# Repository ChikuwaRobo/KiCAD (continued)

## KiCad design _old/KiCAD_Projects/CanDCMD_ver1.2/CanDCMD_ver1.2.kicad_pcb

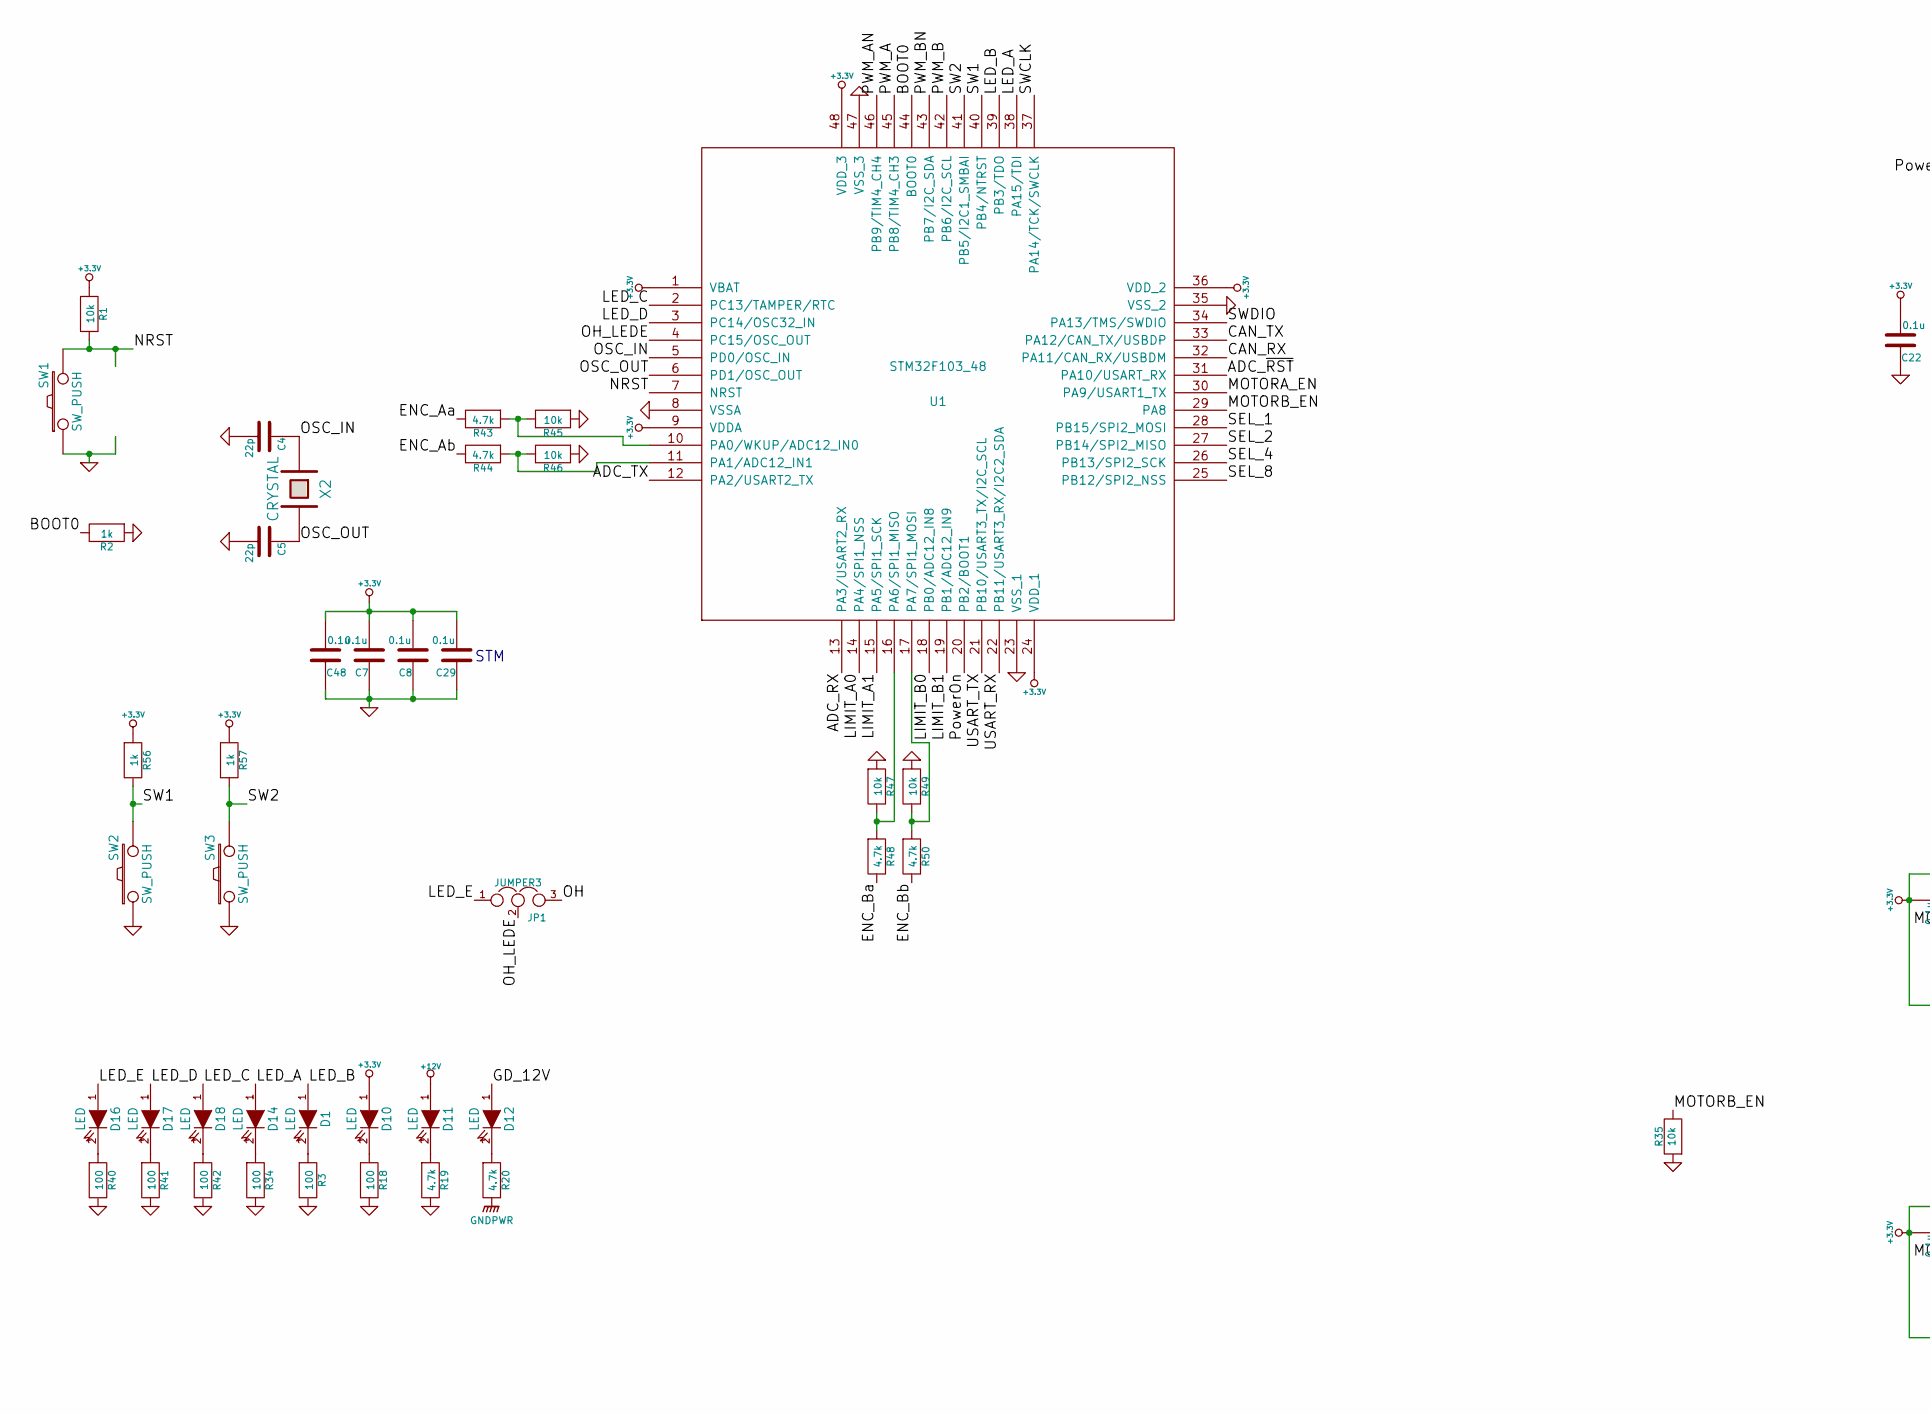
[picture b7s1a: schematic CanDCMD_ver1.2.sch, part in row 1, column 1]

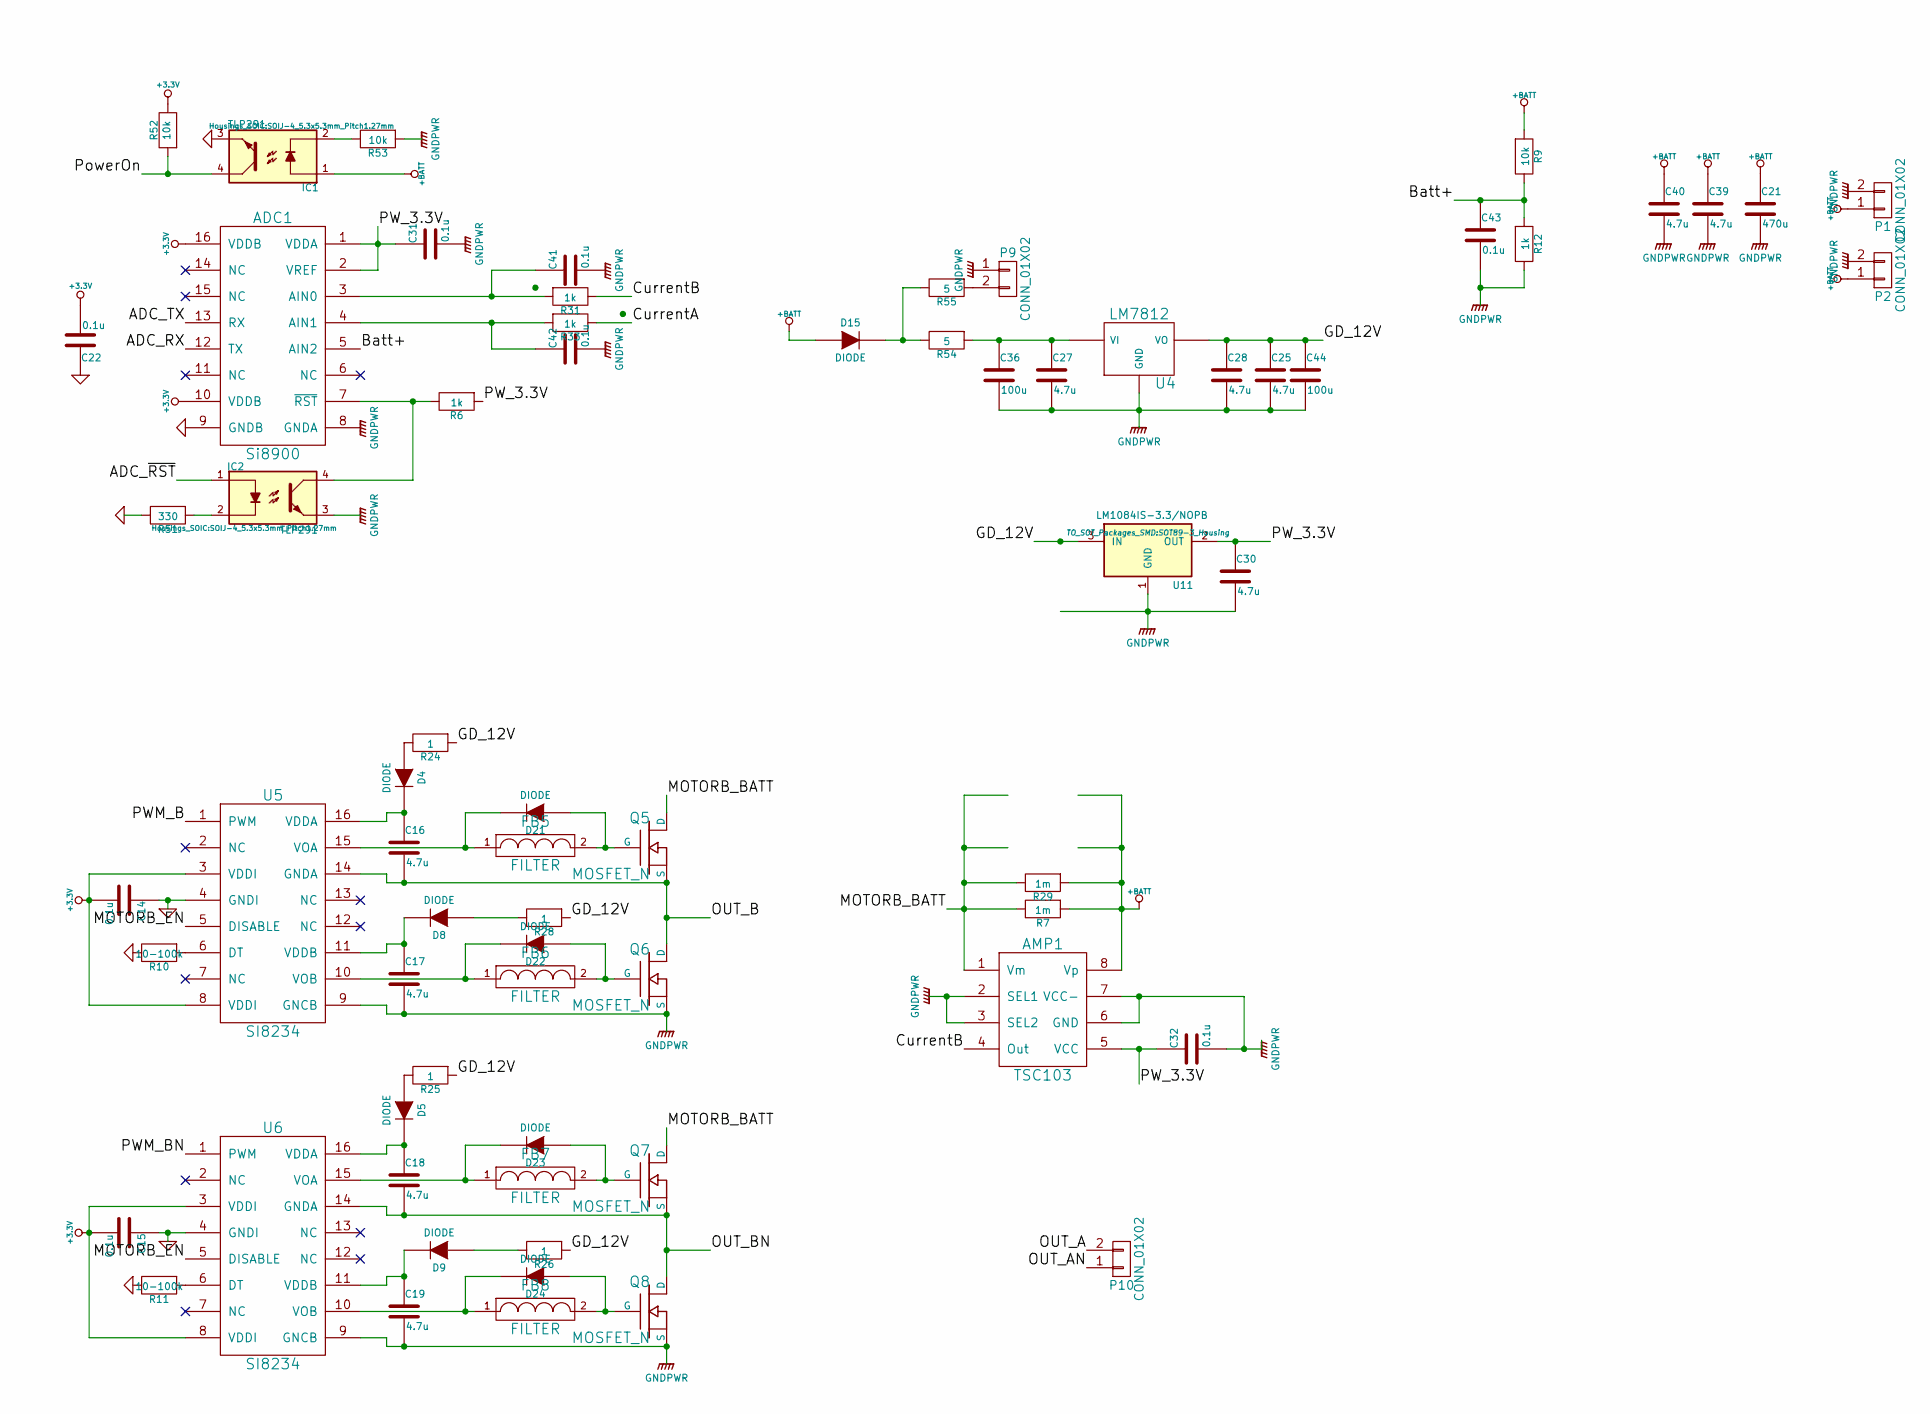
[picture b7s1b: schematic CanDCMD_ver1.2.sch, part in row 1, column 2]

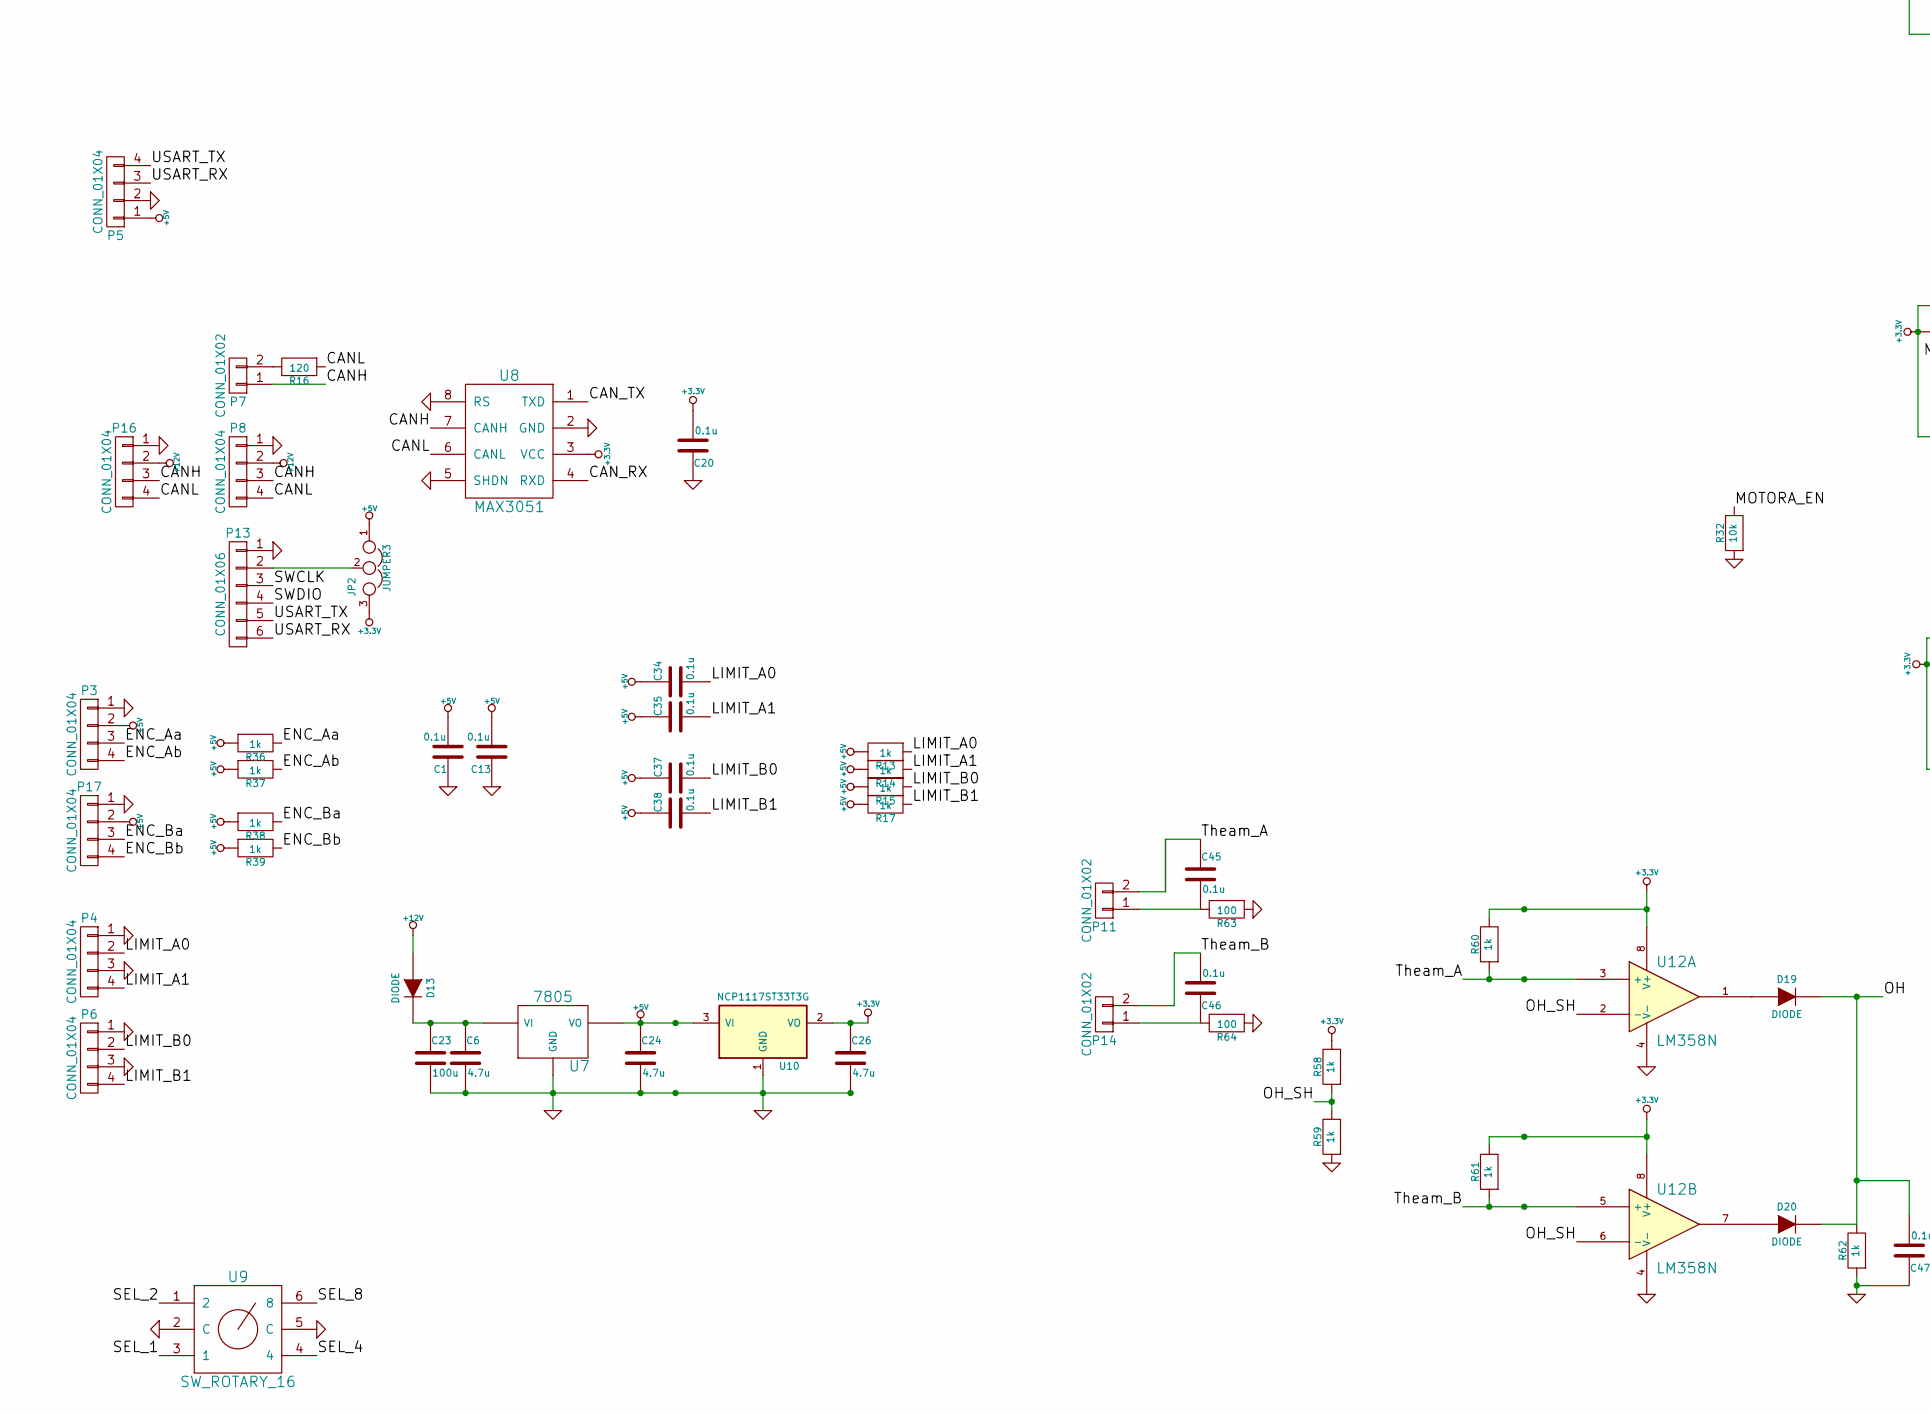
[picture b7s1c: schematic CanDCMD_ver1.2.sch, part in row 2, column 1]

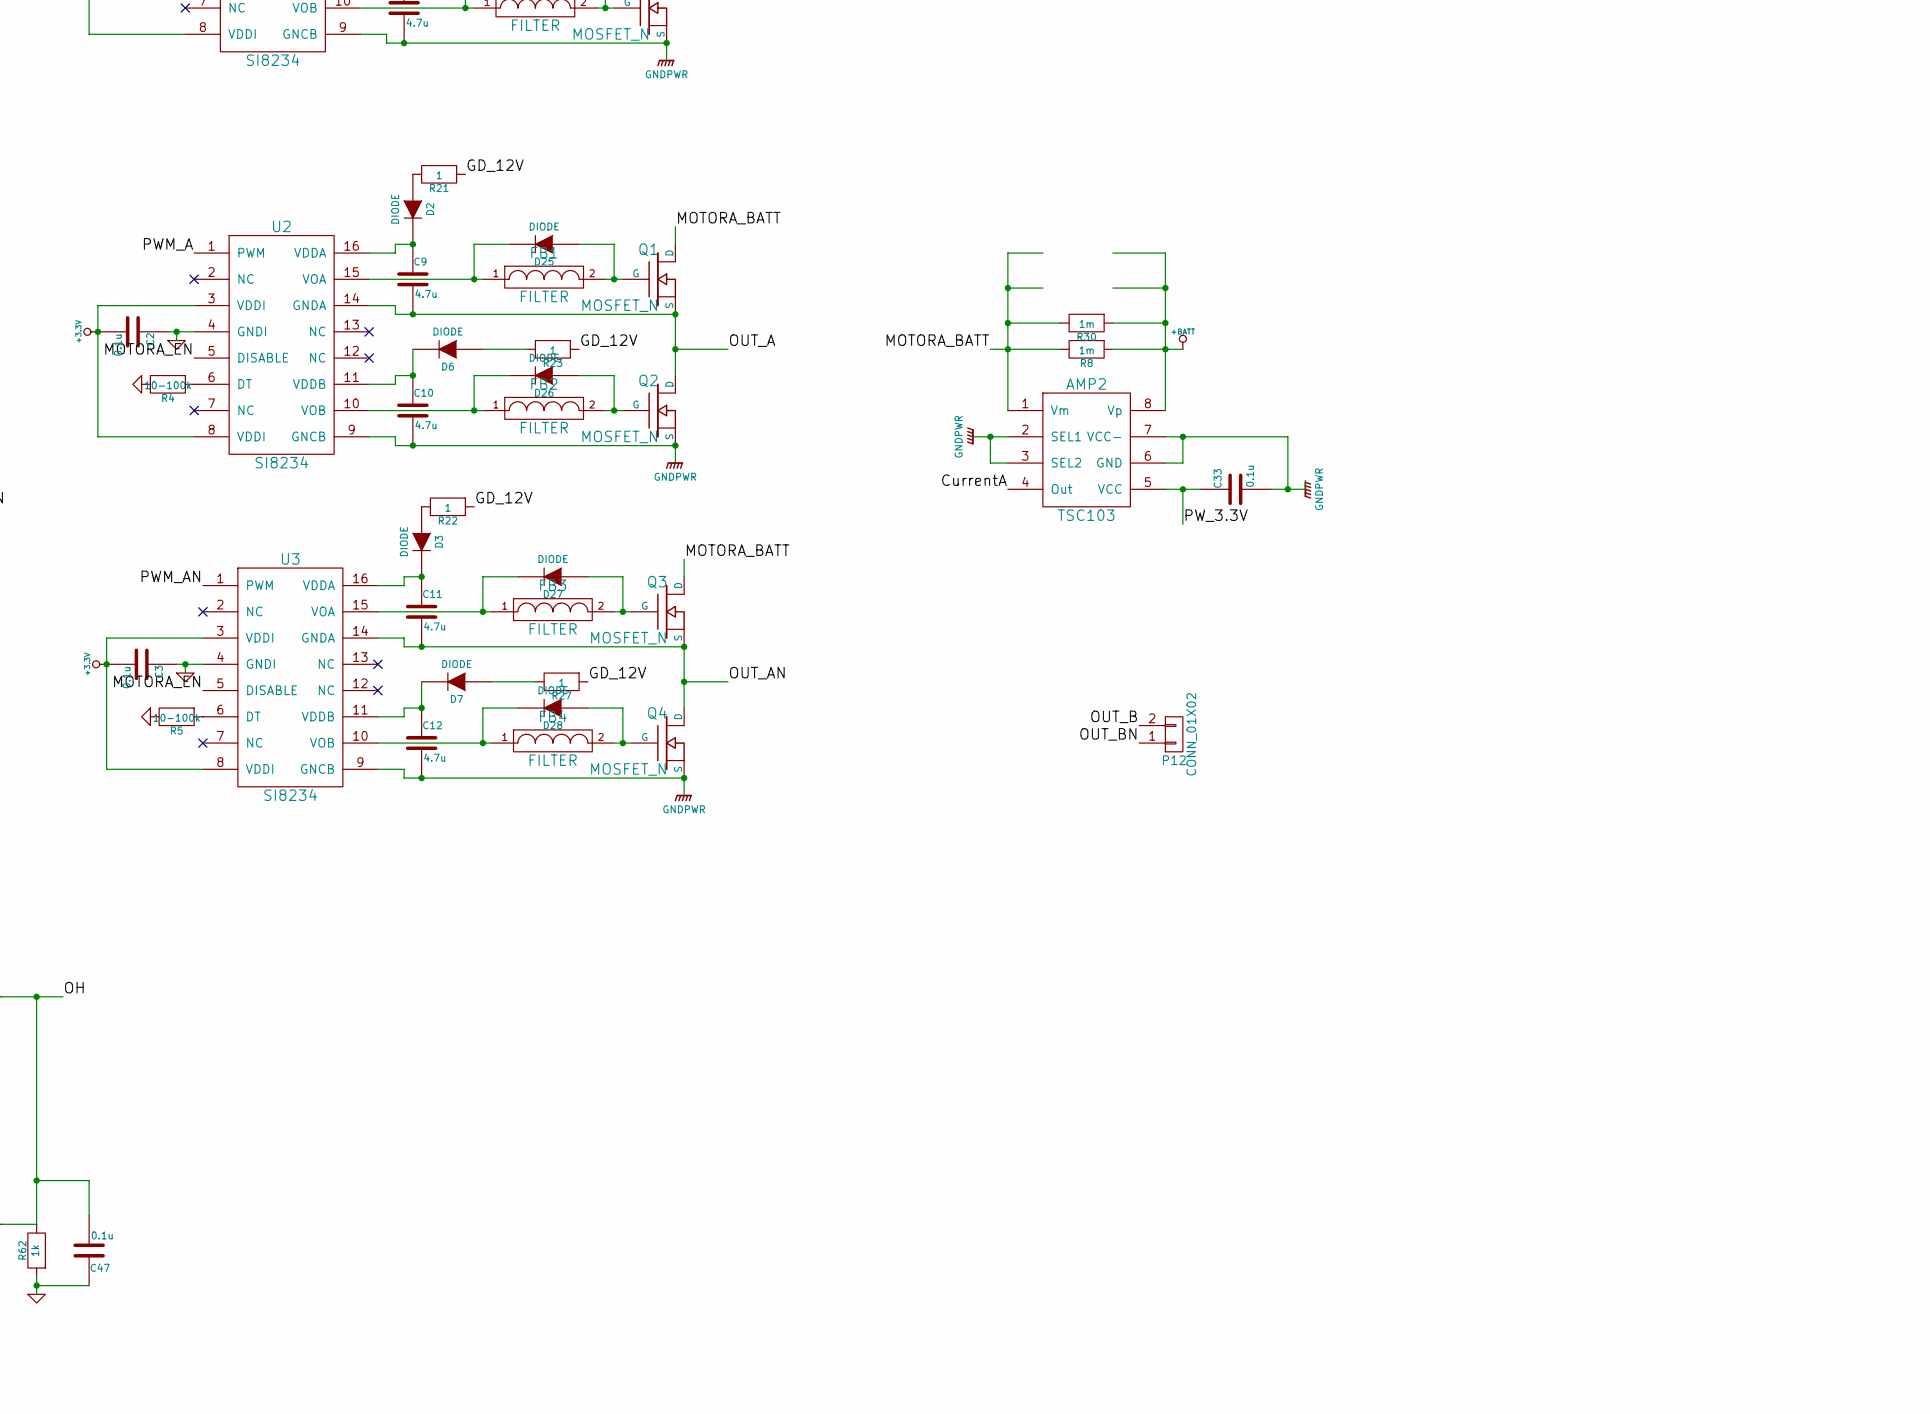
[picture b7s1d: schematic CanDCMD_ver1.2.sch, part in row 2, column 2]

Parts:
ADC1: Si8900; SOIC-16_7.5x10.3mm_Pitch1.27mm
AMP1, AMP2: TSC103; SOIC-8_3.9x4.9mm_Pitch1.27mm
C1, C2, C3, C7, C8, C13, C14, C15, C20, C22, C29, C31, C32, C33, C34, C35, C37, C38, C41, C42, C43, C45, C46, C47, C48: 0.1u; C1608_WP
C4, C5: 22p; C1608_WP
C6, C9, C10, C11, C12, C16, C17, C18, C19, C24, C25, C26, C27, C28, C30, C39, C40: 4.7u; C3216
C21: 470u; C_Radial_D12.5_L25_P5
C23, C36, C44: 100u; C_Radial_D6.3_L11.2_P2.5
D1, D10, D11, D12, D14, D16, D17, D18: LED; C1608_WP
D2, D3, D4, D5, D6, D7, D8, D9, D19, D20, D21, D22, D23, D24, D25, D26, D27, D28: DIODE; C1608_WP
D13, D15: DIODE; C3216
FB1, FB2, FB3, FB4, FB5, FB6, FB7, FB8: FILTER; C1608_WP
IC1, IC2: TLP291; SOIJ-4_5.3x5.3mm_Pitch1.27mm
JP1, JP2: JUMPER3; GS3
P1: CONN_01X02; DEANS_T_M
P2: CONN_01X02; DEANS_T_F
P3, P4, P6, P8, P16, P17: CONN_01X04; XA_4LC
P5: CONN_01X04; Socket_Strip_Straight_1x04
P7: CONN_01X02; Pin_Header_Straight_1x02
P9: CONN_01X02; XA_2T
P10, P12: CONN_01X02; DEANS_T_F_minPad
P11, P14: CONN_01X02; C3216_S
P13: CONN_01X06; ZH_6T
Q1, Q2, Q3, Q4, Q5, Q6, Q7, Q8: MOSFET_N; D2-PAK_compact
R1, R9, R32, R35, R45, R46, R47, R49, R52, R53: 10k; C1608_WP
R2, R6, R12, R13, R14, R15, R17, R31, R33, R36, R37, R38, R39, R56, R57, R58, R59, R60, R61, R62: 1k; C1608_WP
R3, R18, R34, R40, R41, R42, R63, R64: 100; C1608_WP
R4, R5, R10, R11: 10-100k; C1608_WP
R7, R8, R29, R30: 1m; R5025
R16: 120; C1608_WP
R19, R20, R43, R44, R48, R50: 4.7k; C1608_WP
R21, R22, R23, R24, R25, R26, R27, R28: 1; C1608_WP
R51: 330; C1608_WP
R54, R55: 5; R_2812
SW1, SW2, SW3: SW_PUSH; RP_SMD_Button
U1: STM32F103_48; LQFP-48_7x7mm_Pitch0.5mm
U2, U3, U5, U6: SI8234; SOIC-16_3.9x9.9mm_Pitch1.27mm
U4: LM7812; TO-252-2Lead_regu
U7: 7805; TO-252-2Lead_regu
U8: MAX3051; SOIC-8_3.9x4.9mm_Pitch1.27mm
U9: SW_ROTARY_16; rotary_0F
U10: NCP1117ST33T3G; SOT-223_reg
U11: LM1084IS-3.3/NOPB; SOT89-3_Housing
U12: LM358N; SOIC-8_3.9x4.9mm_Pitch1.27mm
X2: CRYSTAL; ABM3_2pads

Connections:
+3.3V: ADC1.10 (VDDB), ADC1.16 (VDDB), C2.2, C3.2, C7.2, C8.2, C14.2, C15.2, C20.2, C22.2, C26.1, C29.2, C48.2, D10.1 (A), JP2.3, R1.1, R52.2, R56.1, R57.1, R58.2, R60.2, R61.2, U1.1 (VBAT), U1.9 (VDDA), U1.24 (VDD_1), U1.36 (VDD_2), U1.48 (VDD_3), U2.3 (VDDI), U2.8 (VDDI), U3.3 (VDDI), U3.8 (VDDI), U5.3 (VDDI), U5.8 (VDDI), U6.3 (VDDI), U6.8 (VDDI), U8.3 (VCC), U10.2 (VO), U12.8 (V+)
+5V: C1.2, C13.2, C24.1, C34.1, C35.1, C37.1, C38.1, JP2.1, P3.2, P5.1, P17.2, R13.2, R14.2, R15.2, R17.2, R36.1, R37.1, R38.1, R39.1, U7.VO, U10.3 (VI)
+12V: D11.1 (A), D13.1 (A), P8.2, P16.2
+BATT: AMP1.8 (Vp), AMP2.8 (Vp), C21.1, C39.1, C40.1, D15.1 (A), IC1.1, P1.1, P2.1, R7.1, R8.1, R9.1, R29.1, R30.1
/ADC_RX: ADC1.12 (TX), U1.13 (PA3/USART2_RX)
/ADC_TX: ADC1.13 (RX), U1.12 (PA2/USART2_TX)
/ADC_~RST: IC2.1, U1.31 (PA10/USART_RX)
/BOOT0: R2.2, U1.44 (BOOT0)
/Batt+: ADC1.5 (AIN2), C43.1, R9.2, R12.1
/CANH: P7.1, P8.3, P16.3, U8.7 (CANH)
/CANL: P8.4, P16.4, R16.1, U8.6 (CANL)
/CAN_RX: U1.32 (PA11/CAN_RX/USBDM), U8.4 (RXD)
/CAN_TX: U1.33 (PA12/CAN_TX/USBDP), U8.1 (TXD)
/CurrentA: AMP2.4 (Out), R33.2
/CurrentB: AMP1.4 (Out), R31.2
/ENC_Aa: P3.3, R36.2, R43.2
/ENC_Ab: P3.4, R37.2, R44.2
/ENC_Ba: P17.3, R38.2, R48.2
/ENC_Bb: P17.4, R39.2, R50.2
/GD_12V: C25.1, C28.1, C44.1, D12.1 (A), R21.1, R22.1, R23.1, R24.1, R25.1, R26.1, R27.1, R28.1, U4.VO, U11.3 (IN)
/LED_A: D14.1 (A), U1.38 (PA15/TDI)
/LED_B: D1.1 (A), U1.39 (PB3/TDO)
/LED_C: D18.1 (A), U1.2 (PC13/TAMPER/RTC)
/LED_D: D17.1 (A), U1.3 (PC14/OSC32_IN)
/LED_E: D16.1 (A), JP1.1
/LIMIT_A0: C34.2, P4.2, R13.1, U1.14 (PA4/SPI1_NSS)
/LIMIT_A1: C35.2, P4.4, R14.1, U1.15 (PA5/SPI1_SCK)
/LIMIT_B0: C37.2, P6.2, R15.1, U1.18 (PB0/ADC12_IN8)
/LIMIT_B1: C38.2, P6.4, R17.1, U1.19 (PB1/ADC12_IN9)
/MOTORA_BATT: AMP2.1 (Vm), Q1.D, Q3.D, R8.2, R30.2
/MOTORA_EN: R32.2, U1.30 (PA9/USART1_TX), U2.5 (DISABLE), U3.5 (DISABLE)
/MOTORB_BATT: AMP1.1 (Vm), Q5.D, Q7.D, R7.2, R29.2
/MOTORB_EN: R35.2, U1.29 (PA8), U5.5 (DISABLE), U6.5 (DISABLE)
/NRST: R1.2, SW1.2, U1.7 (NRST)
/OH: C47.2, D19.2 (K), D20.2 (K), JP1.3, R62.2
/OH_LEDE: JP1.2, U1.4 (PC15/OSC_OUT)
/OH_SH: R58.1, R59.2, U12.2 (-), U12.6 (-)
/OSC_IN: C4.1, U1.5 (PD0/OSC_IN), X2.1
/OSC_OUT: C5.1, U1.6 (PD1/OSC_OUT), X2.2
/OUT_A: C9.2, P10.2, Q1.S, Q2.D, U2.14 (GNDA)
/OUT_AN: C11.2, P10.1, Q3.S, Q4.D, U3.14 (GNDA)
/OUT_B: C16.2, P12.2, Q5.S, Q6.D, U5.14 (GNDA)
/OUT_BN: C18.2, P12.1, Q7.S, Q8.D, U6.14 (GNDA)
/PWM_A: U1.45 (PB8/TIM4_CH3), U2.1 (PWM)
/PWM_AN: U1.46 (PB9/TIM4_CH4), U3.1 (PWM)
/PWM_B: U1.42 (PB6/I2C_SCL), U5.1 (PWM)
/PWM_BN: U1.43 (PB7/I2C_SDA), U6.1 (PWM)
/PW_3.3V: ADC1.1 (VDDA), ADC1.2 (VREF), AMP1.5 (VCC), AMP2.5 (VCC), C30.1, C31.1, C32.1, C33.1, R6.1, U11.2 (OUT)
/PowerOn: IC1.4, R52.1, U1.20 (PB2/BOOT1)
/SEL_1: U1.28 (PB15/SPI2_MOSI), U9.3 (1)
/SEL_2: U1.27 (PB14/SPI2_MISO), U9.1 (2)
/SEL_4: U1.26 (PB13/SPI2_SCK), U9.4
/SEL_8: U1.25 (PB12/SPI2_NSS), U9.6 (8)
/SW1: R56.2, SW2.2, U1.40 (PB4/NTRST)
/SW2: R57.2, SW3.2, U1.41 (PB5/I2C1_SMBAI)
/SWCLK: P13.3, U1.37 (PA14/TCK/SWCLK)
/SWDIO: P13.4, U1.34 (PA13/TMS/SWDIO)
/Theam_A: C45.1, P11.2, R60.1, U12.3 (+)
/Theam_B: C46.2, P14.2, R61.1, U12.5 (+)
/USART_RX: P5.3, P13.6, U1.22 (PB11/USART3_RX/I2C2_SDA)
/USART_TX: P5.4, P13.5, U1.21 (PB10/USART3_TX/I2C_SCL)
GND: ADC1.9 (GNDB), C1.1, C2.1, C3.1, C4.2, C5.2, C6.2, C7.1, C8.1, C13.1, C14.1, C15.1, C20.1, C22.1, C23.2, C24.2, C26.2, C29.1, C47.1, C48.1, IC1.3, P3.1, P4.1, P4.3, P5.2, P6.1, P6.3, P8.1, P13.1, P16.1, P17.1, R2.1, R3.2, R4.2, R5.2, R10.2, R11.2, R18.2, R19.2, R32.1, R34.2, R35.1, R40.2, R41.2, R42.2, R45.1, R46.1, R47.1, R49.1, R51.2, R59.1, R62.1, R63.1, R64.1, SW1.1, SW2.1, SW3.1, U1.8 (VSSA), U1.23 (VSS_1), U1.35 (VSS_2), U1.47 (VSS_3), U2.4 (GNDI), U3.4 (GNDI), U5.4 (GNDI), U6.4 (GNDI), U7.GND, U8.2 (GND), U8.5 (SHDN), U8.8 (RS), U9.2 (C), U9.5 (C), U10.1 (GND), U12.4 (V-)
GNDPWR: ADC1.8 (GNDA), AMP1.2 (SEL1), AMP1.3 (SEL2), AMP1.6 (GND), AMP1.7 (VCC-), AMP2.2 (SEL1), AMP2.3 (SEL2), AMP2.6 (GND), AMP2.7 (VCC-), C10.2, C12.2, C17.2, C19.2, C21.2, C25.2, C27.2, C28.2, C30.2, C31.2, C32.2, C33.2, C36.2, C39.2, C40.2, C41.2, C42.2, C43.2, C44.2, IC2.3, P1.2, P2.2, P9.1, Q2.S, Q4.S, Q6.S, Q8.S, R12.2, R20.2, R53.1, U2.9 (GNCB), U3.9 (GNCB), U4.GND, U5.9 (GNCB), U6.9 (GNCB), U11.1 (GND)
unnamed: ADC1.3 (AIN0), C41.1, R31.1
unnamed: ADC1.4 (AIN1), C42.1, R33.1
unnamed: ADC1.7 (~RST), IC2.4, R6.2
unnamed: C9.1, D2.2 (K), U2.16 (VDDA)
unnamed: C10.1, D6.2 (K), U2.11 (VDDB)
unnamed: C11.1, D3.2 (K), U3.16 (VDDA)
unnamed: C12.1, D7.2 (K), U3.11 (VDDB)
unnamed: C16.1, D4.2 (K), U5.16 (VDDA)
unnamed: C17.1, D8.2 (K), U5.11 (VDDB)
unnamed: C18.1, D5.2 (K), U6.16 (VDDA)
unnamed: C19.1, D9.2 (K), U6.11 (VDDB)
unnamed: C6.1, C23.1, D13.2 (K), U7.VI
unnamed: C27.1, C36.1, R54.1, U4.VI
unnamed: C45.2, P11.1, R63.2
unnamed: C46.1, P14.1, R64.2
unnamed: D1.2 (K), R3.1
unnamed: D2.1 (A), R21.2
unnamed: D3.1 (A), R22.2
unnamed: D4.1 (A), R24.2
unnamed: D5.1 (A), R25.2
unnamed: D6.1 (A), R23.2
unnamed: D7.1 (A), R27.2
unnamed: D8.1 (A), R28.2
unnamed: D9.1 (A), R26.2
unnamed: D10.2 (K), R18.1
unnamed: D11.2 (K), R19.1
unnamed: D12.2 (K), R20.1
unnamed: D14.2 (K), R34.1
unnamed: D15.2 (K), R54.2, R55.2
unnamed: D16.2 (K), R40.1
unnamed: D17.2 (K), R41.1
unnamed: D18.2 (K), R42.1
unnamed: D19.1 (A), U12.1
unnamed: D20.1 (A), U12.7
unnamed: D21.1 (A), FB5.2, Q5.G
unnamed: D21.2 (K), FB5.1, U5.15 (VOA)
unnamed: D22.1 (A), FB6.2, Q6.G
unnamed: D22.2 (K), FB6.1, U5.10 (VOB)
unnamed: D23.1 (A), FB7.2, Q7.G
unnamed: D23.2 (K), FB7.1, U6.15 (VOA)
unnamed: D24.1 (A), FB8.2, Q8.G
unnamed: D24.2 (K), FB8.1, U6.10 (VOB)
unnamed: D25.1 (A), FB1.2, Q1.G
unnamed: D25.2 (K), FB1.1, U2.15 (VOA)
unnamed: D26.1 (A), FB2.2, Q2.G
unnamed: D26.2 (K), FB2.1, U2.10 (VOB)
unnamed: D27.1 (A), FB3.2, Q3.G
unnamed: D27.2 (K), FB3.1, U3.15 (VOA)
unnamed: D28.1 (A), FB4.2, Q4.G
unnamed: D28.2 (K), FB4.1, U3.10 (VOB)
unnamed: IC1.2, R53.2
unnamed: IC2.2, R51.1
unnamed: JP2.2, P13.2
unnamed: P7.2, R16.2
unnamed: P9.2, R55.1
unnamed: R4.1, U2.6 (DT)
unnamed: R5.1, U3.6 (DT)
unnamed: R10.1, U5.6 (DT)
unnamed: R11.1, U6.6 (DT)
unnamed: R43.1, R45.2, U1.10 (PA0/WKUP/ADC12_IN0)
unnamed: R44.1, R46.2, U1.11 (PA1/ADC12_IN1)
unnamed: R47.2, R48.1, U1.16 (PA6/SPI1_MISO)
unnamed: R49.2, R50.1, U1.17 (PA7/SPI1_MOSI)

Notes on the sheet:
STM

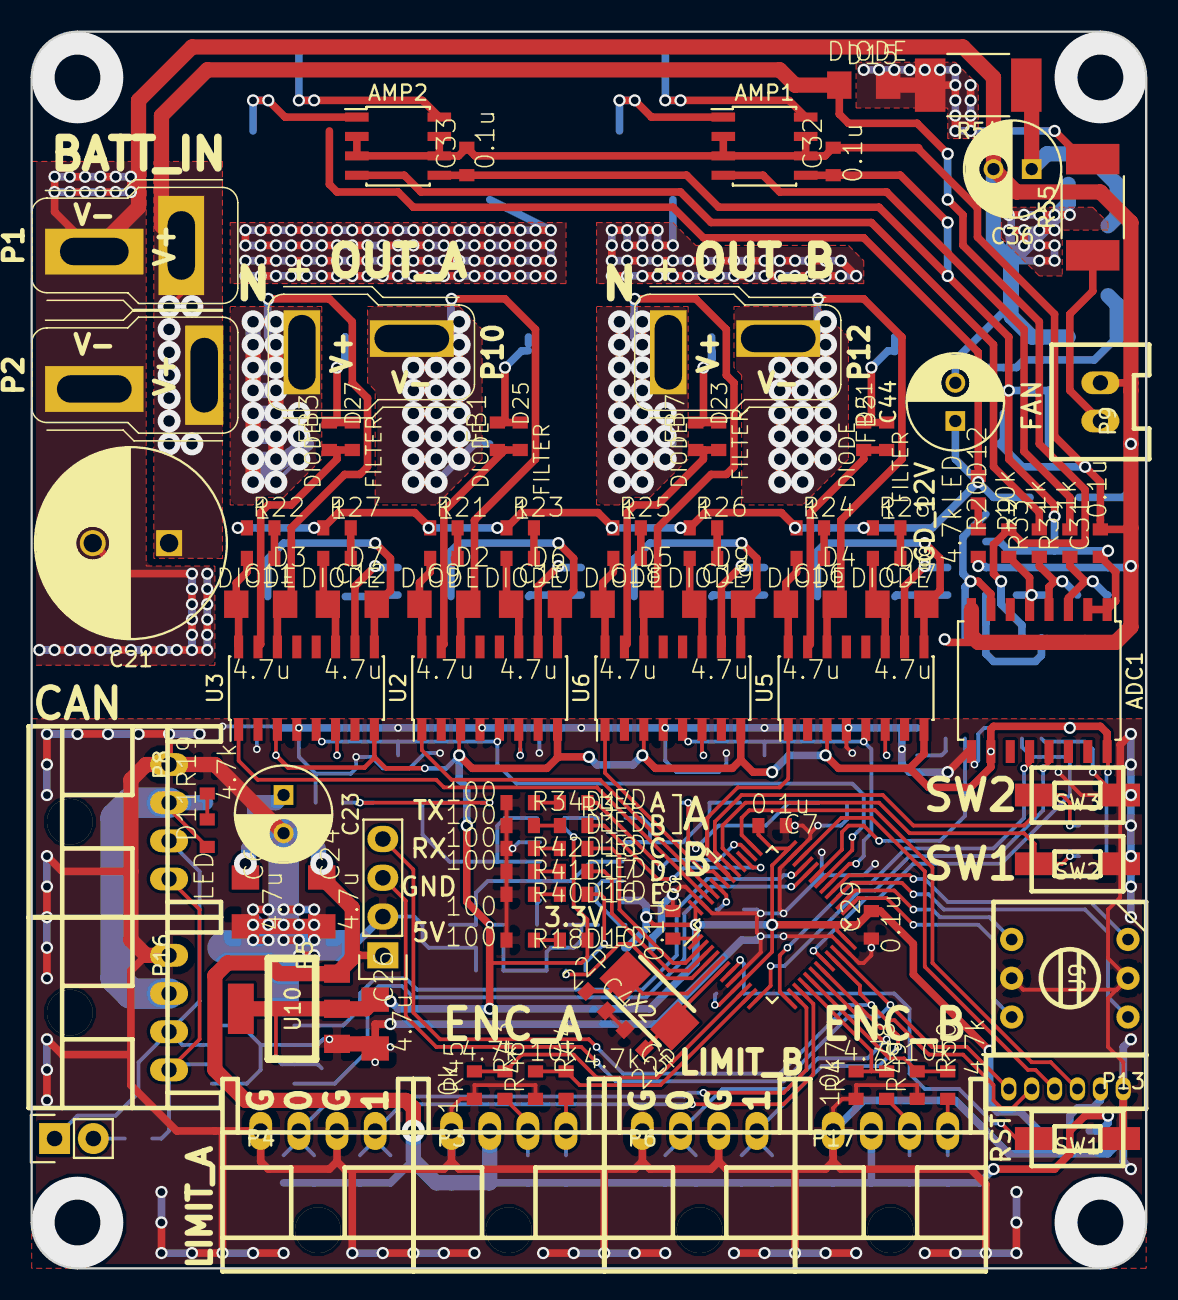
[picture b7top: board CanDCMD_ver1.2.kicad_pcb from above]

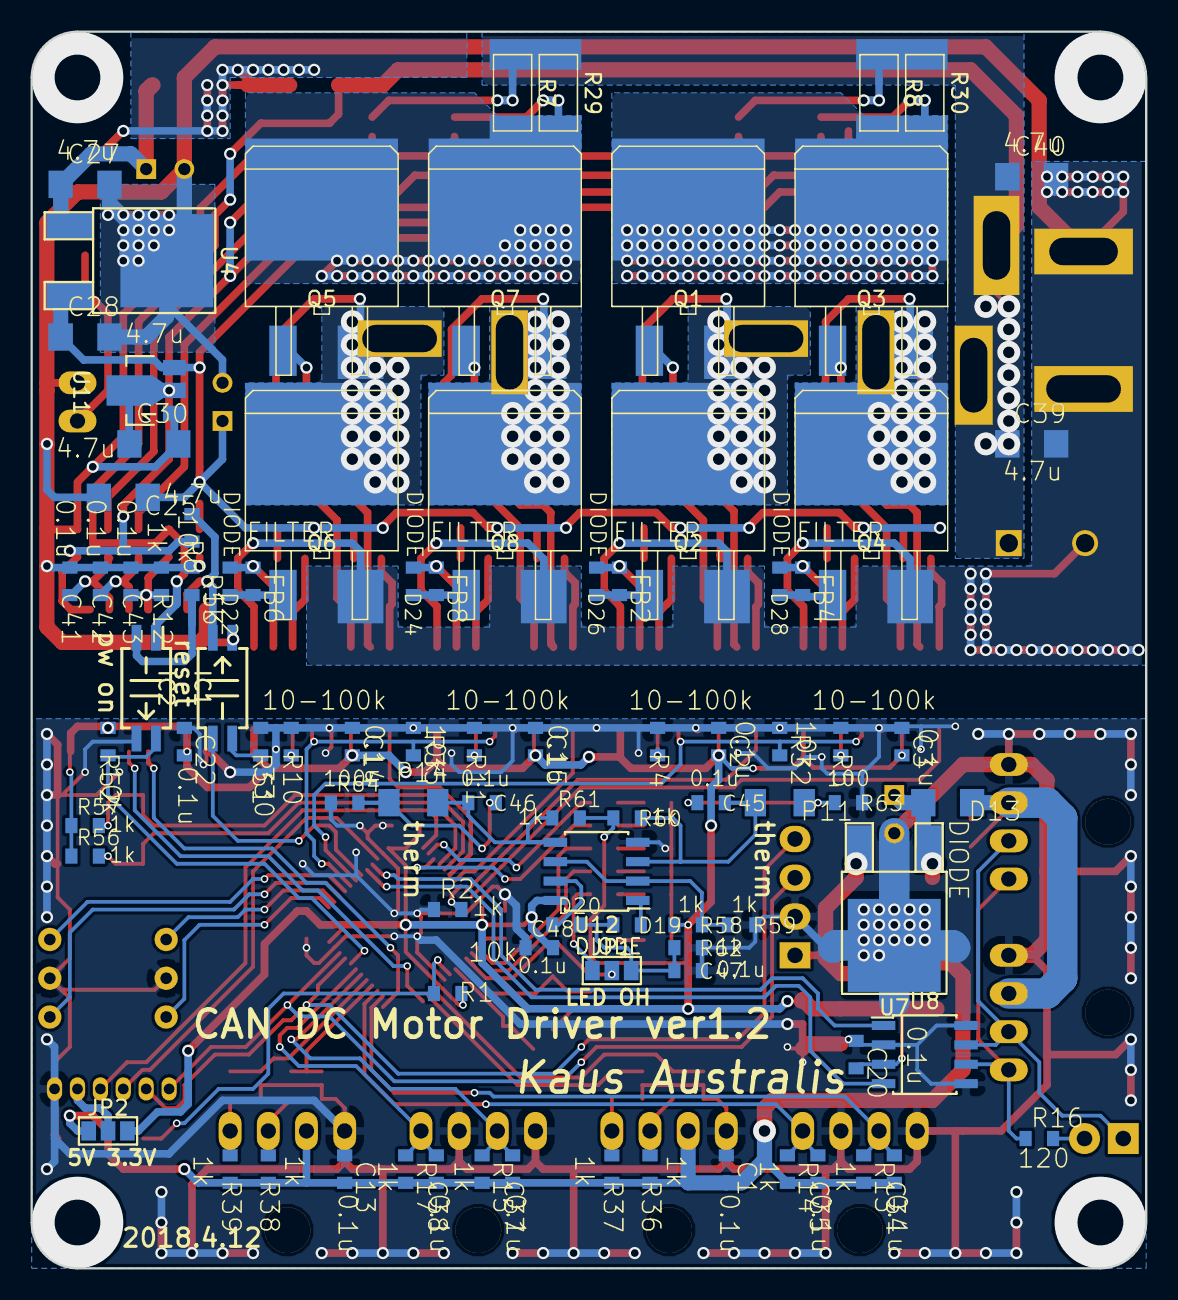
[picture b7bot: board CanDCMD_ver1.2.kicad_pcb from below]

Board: 2 copper layers, 73.0 x 81.0 mm, 195 parts (90 on the bottom side), 126 nets.

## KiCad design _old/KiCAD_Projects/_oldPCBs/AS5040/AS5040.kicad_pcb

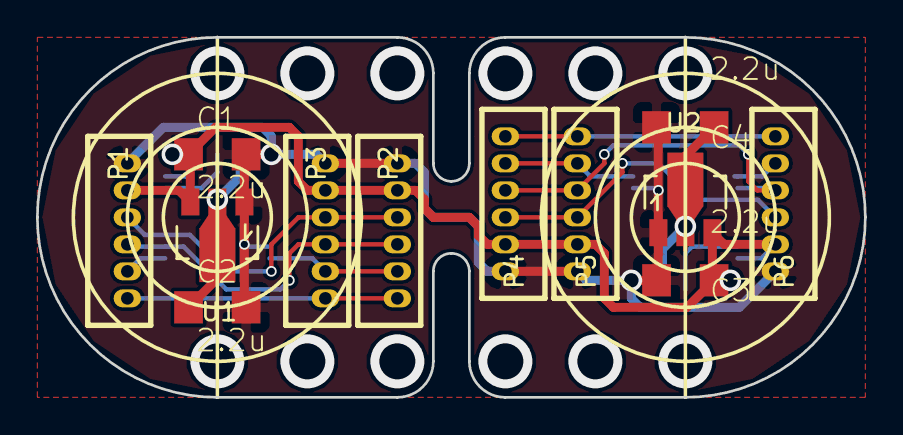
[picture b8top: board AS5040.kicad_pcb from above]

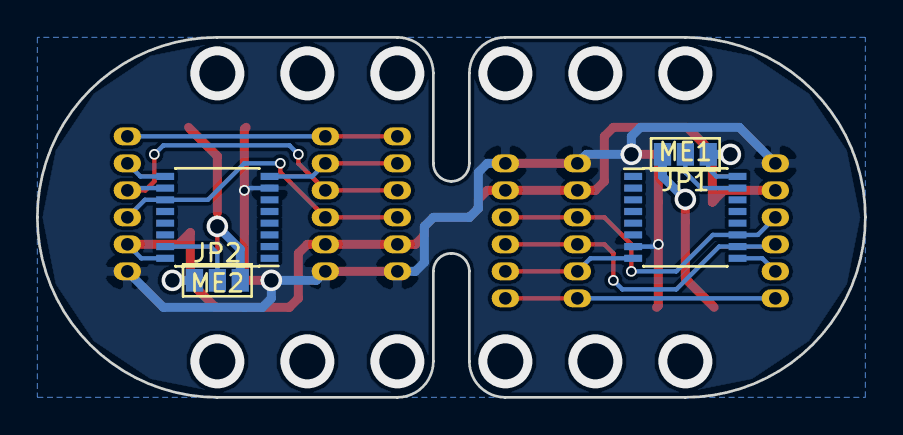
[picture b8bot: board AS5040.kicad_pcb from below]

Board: 2 copper layers, 46.0 x 20.0 mm, 16 parts (4 on the bottom side), 16 nets.

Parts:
C1, C2, C3, C4: 2.2u; C3216
JP1, JP2: JUMPER3; GS3
ME1, ME2: AS504x; SSOP-16_4.4x5.2mm_Pitch0.65mm
P1, P2, P3, P4, P5, P6: CONN_01X06; ZH_6T
U1, U2: NCP1117ST33T3G; SOT89-3_Housing

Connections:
+5V: C1.1, C3.1, JP1.1, JP2.1, ME1.16, ME2.16, P1.2, P2.2, P3.2, P4.2, P5.2, P6.2, U1.3, U2.3
GND: C1.2, C2.2, C3.2, C4.2, ME1.7, ME2.7, P1.1, P2.1, P3.1, P4.1, P5.1, P6.1, U1.1, U2.1
unnamed: C2.1, JP1.3, U1.2
unnamed: C4.1, JP2.3, U2.2
unnamed: JP1.2, ME1.15
unnamed: JP2.2, ME2.15
unnamed: ME1.8, P2.5, P3.5
unnamed: ME1.9, P1.5
unnamed: ME1.10, P1.4, P2.4, P3.4
unnamed: ME1.11, P1.3, P2.3, P3.3
unnamed: ME2.8, P4.5, P5.5
unnamed: ME2.9, P6.5
unnamed: ME2.10, P4.4, P5.4, P6.4
unnamed: ME2.11, P4.3, P5.3, P6.3
unnamed: P1.6, P2.6, P3.6
unnamed: P4.6, P5.6, P6.6

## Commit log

2016-03-27 addfiles
2016-03-27 no message
2016-05-17 add IR
2016-06-03 add PCB projects
2016-12-25 SPIアイソレータの追加
2016-12-28 3Dデータ組み合わてテスト
2016-12-31 4.0.5のライブラリを追加｡インダクタの3Dモジュール追加
2017-01-01 F407mini本格的に設計始めた
2017-01-01 F407miniたぶんできた
2017-01-23 単発エンコーダ基板のアドレスセレクタ変更
2017-02-04 rev4.0設計開始
2017-02-04 制御系の配線終わったんじゃね？
2017-02-09 MDver4.0だいたいできた｡絶縁アンプ基板作った｡
2017-02-18 4.0発注かけた｡テレメトリとコンパネ作る
2017-02-19 まともに新電源基板設計始めた
2017-02-24 コンパネおわり｡キャンサー作る
2017-03-04 5.0プロジェクト作った
2017-03-07 ver5.0設計中
2017-03-14 ver5.0と5.0Exの設計終わり｡CAN node ver1.2の設計終わり｡BLMD基板設計開始｡ISO_DCDCver1.1設計開始｡
2017-03-16 セルチェッカー作った｡電源基板ver1.1作った｡ぶっさしMDいじった｡DCDCいじりだした｡
2017-03-18 BLMD設計終わり
2017-03-24 基板発注かけた
2017-03-30 コンパネver1.1作った｡本番仕様サジ電源基板つくった
2017-03-31 明日の加工用データの出力､Cancer用電源基板の再設計
2017-04-05 BLMDver1.1設計大体終わり｡
2017-04-09 BLMDver1.1とCancer用メインのすり合わせ｡BatteryArarmの改良
2017-04-14 発注に向けて調整
2017-04-19 発注した｡古い基板プロジェクトの移動
2017-04-24 ファイル整理+ver1.1プロジェクト
2017-05-01 CanDCMDver1.1設計｡ISO_DCDC_ver1.2はじめた
2017-05-02 発注した｡
2017-05-06 ISO_DCDC_ver1.2の設計終わり｡加工依頼用データだし｡
2017-05-17 電源基板ver1.2加工した｡次ver1.3作るべきかも
2017-05-21 電源ver1.3仮完成｡ラインセンサも一応｡
2017-07-29 Morex系ゴニョゴニョした
2017-10-03 かわロボ基2.0設計中
2017-10-12 かわロボver2.0､中間電圧追加
2017-10-17 中華DCDCやMPU6050､RSproブザーのライブラリ作った+2.0へ反映
2017-10-31 面実装ブザー付けた
2017-12-13 ver1.2設計してる
2017-12-29 KawaRobo_ver1.2だいたいできた
2018-01-03 発注かけた
2018-01-29 Hブリッジドライバ基板作り始めた
2018-01-31 ブラシレス作り始めた(n回目)
2018-02-16 F103mini_rev2.0おわり｡BLDCの部品選定終わったけど電圧フィードバックで詰んだ
2018-02-27 BLDCもだいたい設計終わった
2018-03-05 なにもしていないがなにもしていないではない
2018-03-05 趣味F103ドライバ基板作り始めた(仕様未定)
2018-04-24 CanDCMD_ver1.2作った｡発注した｡
2018-05-26 いろいろやった
2018-07-09 bldc
2018-09-14 BLMD_ver0.1仮
2024-08-17 全てをpush
2024-09-07 全てを追加
2025-07-12 諸々追加
2025-07-18 整理その2
2026-06-08 init
2026-06-08 README.md
2026-06-16 MT6835
